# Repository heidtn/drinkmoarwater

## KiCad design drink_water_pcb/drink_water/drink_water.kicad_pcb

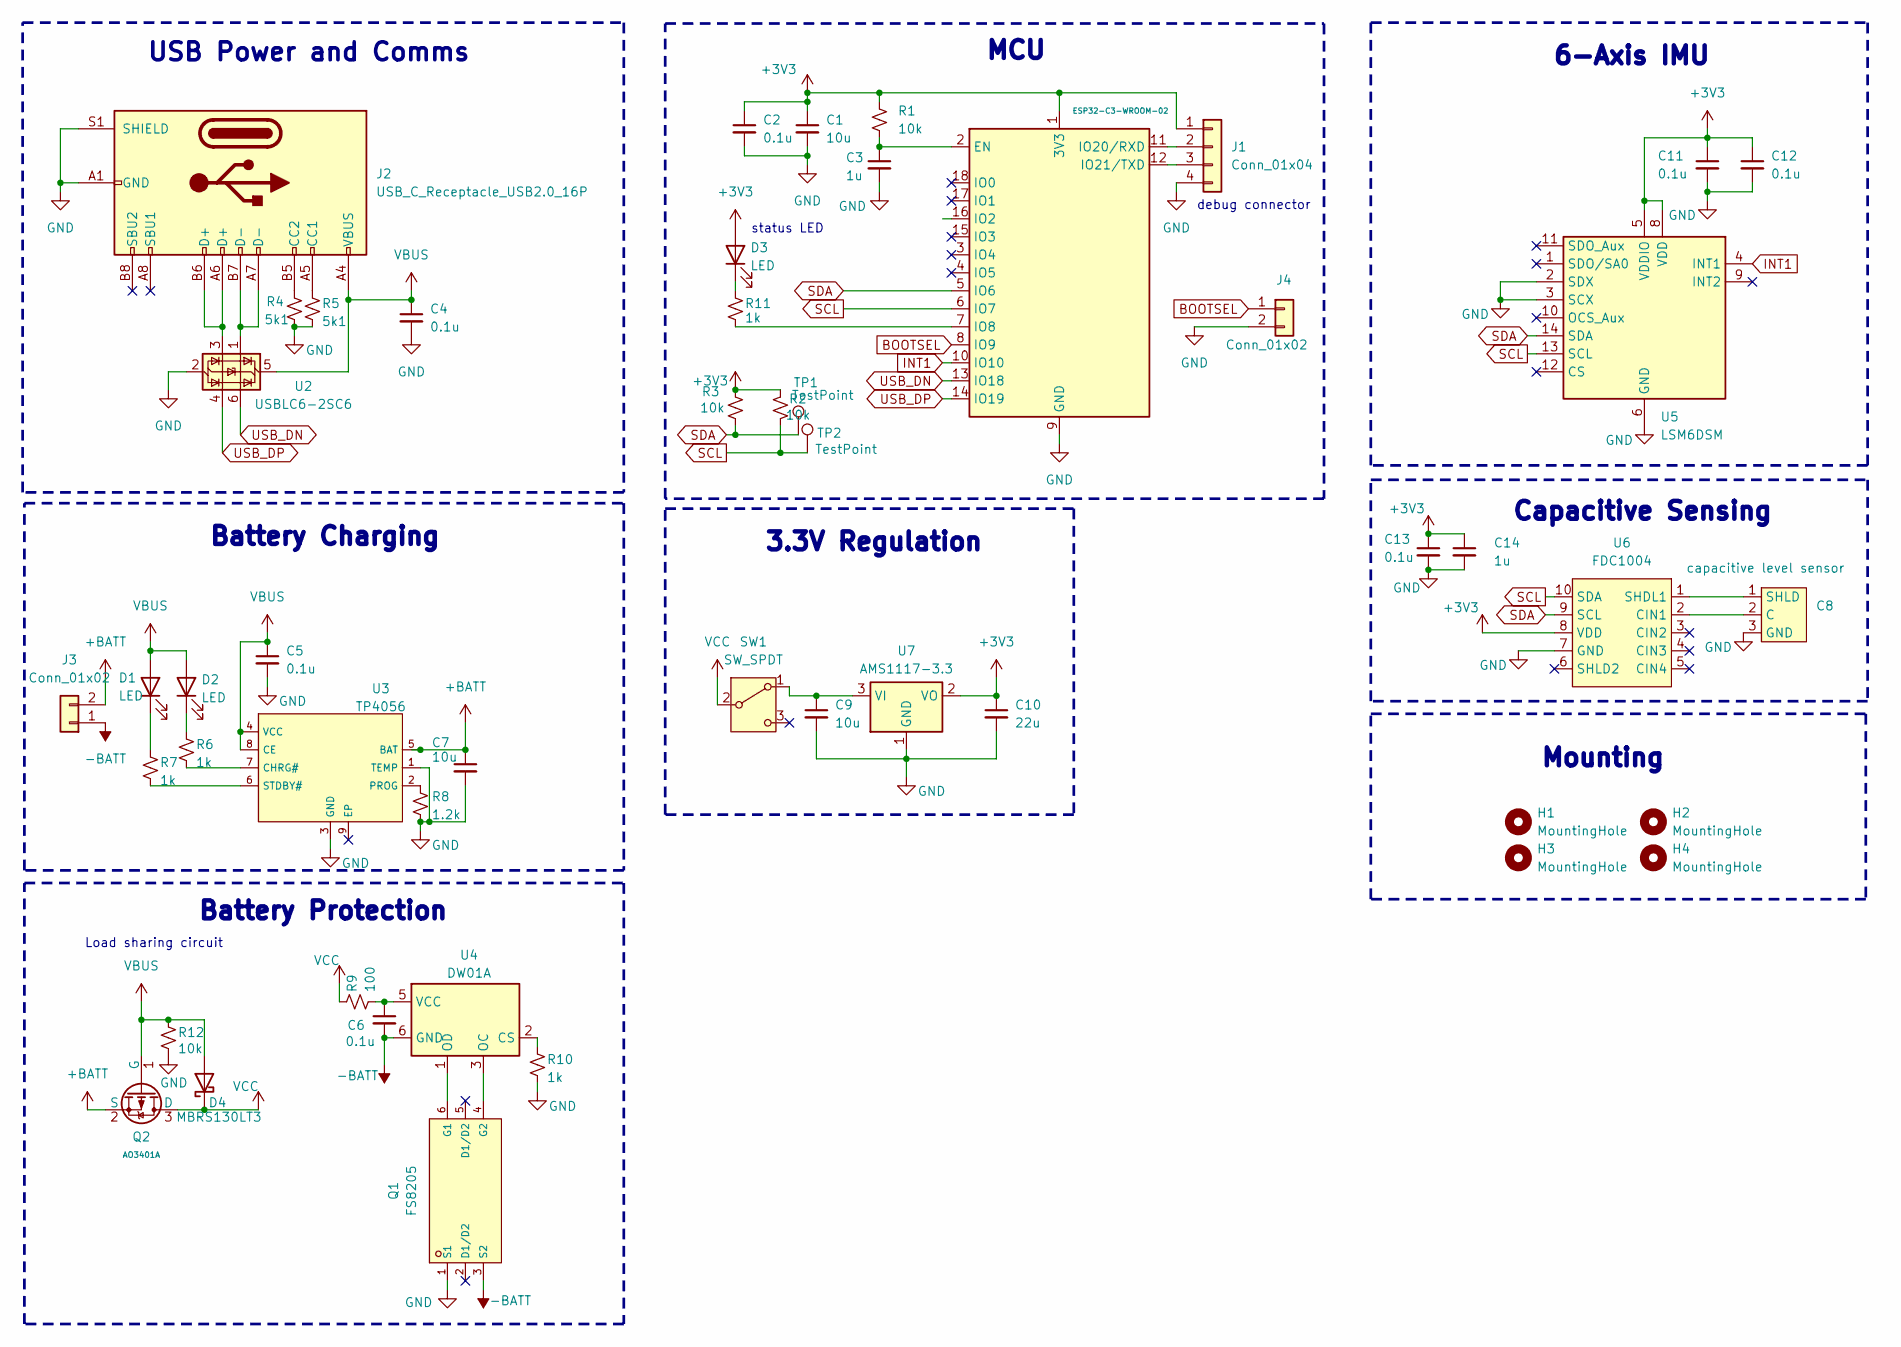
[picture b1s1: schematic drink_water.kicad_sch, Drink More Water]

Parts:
C1, C7, C9: 10u; C_0805_2012Metric
C2, C4, C5, C6, C11, C12, C13: 0.1u; C_0402_1005Metric
C3, C14: 1u; C_0402_1005Metric
C8: capacitive level sensor; level_sensor_footprint
C10: 22u; C_0805_2012Metric
D1, D2, D3: LED; LED_0603_1608Metric
D4: MBRS130LT3; D_SMB
H1, H2, H3, H4: MountingHole; MountingHole_2.7mm_M2.5_Pad_Via
J1: Conn_01x04; JST_GH_BM04B-GHS-TBT_1x04-1MP_P1.25mm_Vertical
J2: USB_C_Receptacle_USB2.0_16P; USB_C_Receptacle_HRO_TYPE-C-31-M-12
J3: Conn_01x02; JST_GH_SM02B-GHS-TB_1x02-1MP_P1.25mm_Horizontal
J4: Conn_01x02; PinHeader_1x02_P2.54mm_Vertical
Q1: FS8205; SOT-23-6; Part HJ8205; LCSC C20069150
Q2: AO3401A; SOT-23; Part AO3401A; LCSC C15127
R1, R2, R3, R12: 10k; R_0402_1005Metric
R4, R5: 5k1; R_0402_1005Metric
R6, R7, R10, R11: 1k; R_0402_1005Metric
R8: 1.2k; R_0402_1005Metric
R9: 100; R_0402_1005Metric
SW1: SW_SPDT; SW_SPDT_PCM12
TP1, TP2: TestPoint; TestPoint_Pad_D1.5mm
U1: ESP32-C3-WROOM-02
U2: USBLC6-2SC6; SOT-23-6
U3: TP4056; ESOP-8_L4.9-W3.9-P1.27-LS6.0-BL-EP; Part TP4056-42-ESOP8; LCSC C16581
U4: DW01A; SOT-23-6
U5: LSM6DSM; LGA-14_3x2.5mm_P0.5mm_LayoutBorder3x4y
U6: FDC1004; MSOP-10_3x3mm_P0.5mm
U7: AMS1117-3.3; SOT-223-3_TabPin2

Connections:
+3V3: C1.1, C2.1, C10.1, C11.1, C12.1, C13.1, C14.1, D3.2 (A), J1.1, R1.1, R2.1, R3.1, U1.1 (3V3), U5.5 (VDDIO), U5.8 (VDD), U6.8 (VDD), U7.2 (VO)
+BATT: C7.1, J3.2, Q2.2 (S), U3.5 (BAT)
-BATT: C6.2, J3.1, Q1.3 (S2), U4.6 (GND)
BOOTSEL: J4.1, U1.8 (IO9)
GND: C1.2, C2.2, C3.2, C4.2, C5.2, C7.2, C8.3 (GND), C9.2, C10.2, C11.2, C12.2, C13.2, C14.2, J1.4, J2.A1 (GND), J2.A12 (GND), J2.B1 (GND), J2.B12 (GND), J2.S1 (SHIELD), J4.2, Q1.1 (S1), R4.2, R5.2, R8.2, R10.2, R12.2, U1.9 (GND), U1.19 (GND), U2.2 (GND), U3.1 (TEMP), U3.3 (GND), U5.2 (SDX), U5.3 (SCX), U5.6 (GND), U5.7 (GND), U6.7 (GND), U7.1 (GND)
INT1: U1.10 (IO10), U5.4 (INT1)
unnamed: C8.2 (C), U6.2 (CIN1)
unnamed: C8.1 (SHLD), U6.1 (SHDL1)
unnamed: D1.1 (K), R7.1
unnamed: D2.1 (K), R6.1
unnamed: D3.1 (K), R11.1
unnamed: J1.2, U1.11 (IO20/RXD)
unnamed: J1.3, U1.12 (IO21/TXD)
unnamed: J2.A5 (CC1), R5.1
unnamed: J2.B5 (CC2), R4.1
unnamed: J2.A6 (D+), J2.B6 (D+), U2.3 (I/O2)
unnamed: J2.A7 (D-), J2.B7 (D-), U2.1 (I/O1)
unnamed: Q1.6 (G1), U4.1 (OD)
unnamed: Q1.4 (G2), U4.3 (OC)
unnamed: C9.1, SW1.1 (A), U7.3 (VI)
unnamed: C3.1, R1.2, U1.2 (EN)
unnamed: R11.2, U1.7 (IO8)
unnamed: R6.2, U3.7 (CHRG#)
unnamed: R8.1, U3.2 (PROG)
unnamed: R7.2, U3.6 (STDBY#)
unnamed: R10.1, U4.2 (CS)
unnamed: C6.1, R9.2, U4.5 (VCC)
SCL: R2.2, TP2.1, U1.6 (IO7), U5.13 (SCL), U6.10 (SDA)
SDA: R3.2, TP1.1, U1.5 (IO6), U5.14 (SDA), U6.9 (SCL)
USB_DN: U1.13 (IO18), U2.6 (I/O1)
USB_DP: U1.14 (IO19), U2.4 (I/O2)
VBUS: C4.1, C5.1, D1.2 (A), D2.2 (A), D4.2 (A), J2.A4 (VBUS), J2.A9 (VBUS), J2.B4 (VBUS), J2.B9 (VBUS), Q2.1 (G), R12.1, U2.5 (VBUS), U3.4 (VCC), U3.8 (CE)
VCC: D4.1 (K), Q2.3 (D), R9.1, SW1.2 (B)

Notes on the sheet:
USB Power and Comms
MCU
Battery Charging
6-Axis IMU
3.3V Regulation
status LED
Load sharing circuit
Capacitive Sensing
Battery Protection
debug connector
Mounting

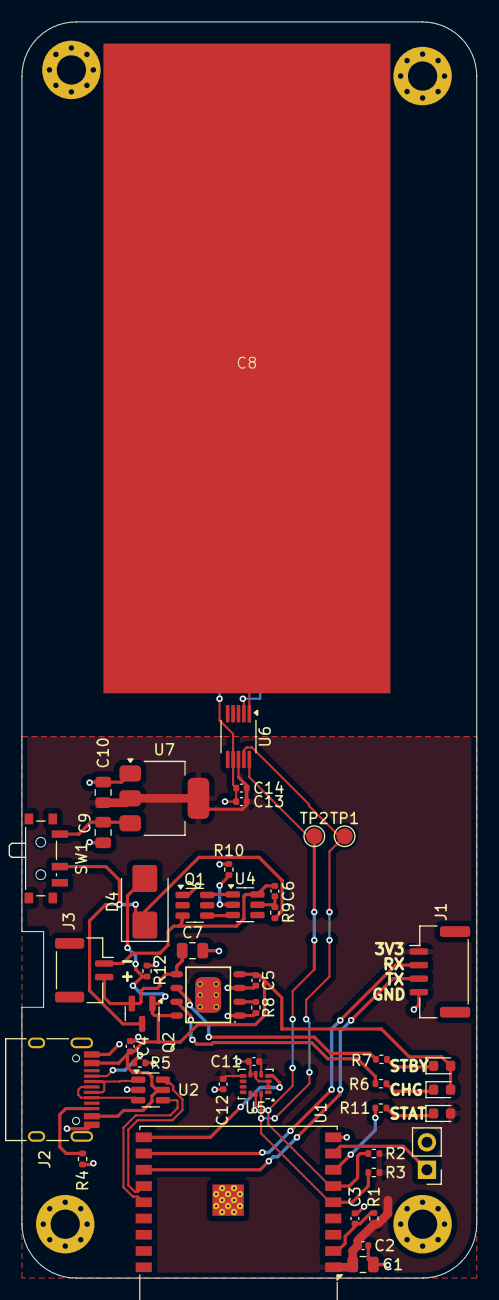
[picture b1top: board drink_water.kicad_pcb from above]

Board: 2 copper layers, 42.0 x 116.0 mm, 51 parts (1 on the bottom side), 33 nets.

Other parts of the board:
Drink Water V0.1.0: https://github.com/heidtn/drinkmoarwater; https___github.com_heidtn_drinkmoarwater

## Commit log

2025-05-17 Initial commit, first schematic version, pre-routing
2025-05-18 Initial layout, pre-route
2025-05-18 Initial version of PCB design
2025-05-18 Shifted USB port proud of board
